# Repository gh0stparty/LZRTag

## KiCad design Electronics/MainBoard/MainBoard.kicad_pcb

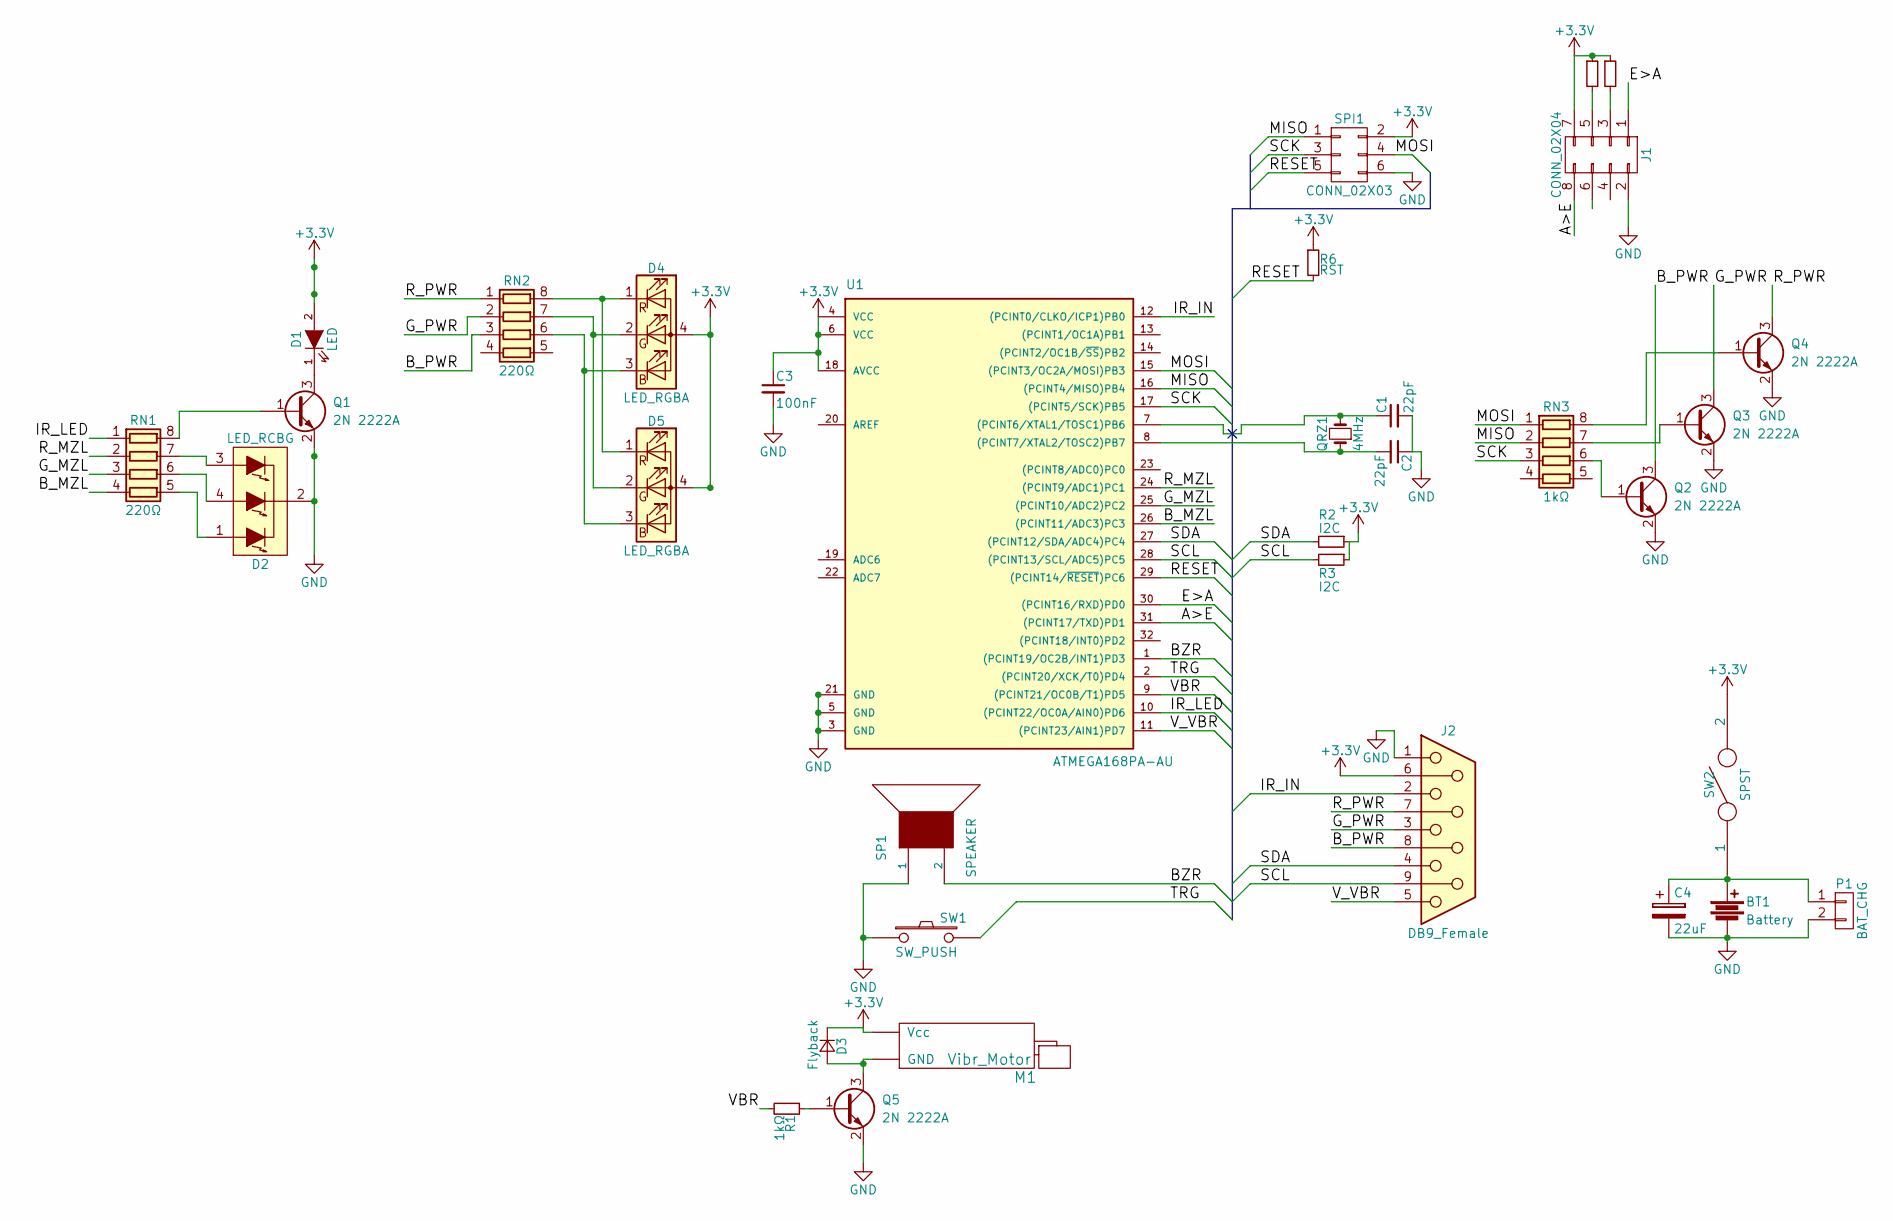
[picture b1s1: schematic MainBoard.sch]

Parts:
BT1: Battery; JST_PH_B2B-PH-K_02x2.00mm_Straight
C1, C2: 22pF; C_0603_HandSoldering
C3: 100nF; R_1210
C4: 22uF; CP_Elec_5x5.3
D1: LED; Pin_Header_Straight_1x02_Pitch2.00mm
D2: LED_RCBG; Pin_Header_Straight_1x04_Pitch2.00mm
D3: Flyback; SOD-323_HandSoldering
D4, D5: LED_RGBA; LED_Cree-PLCC4_3.2x2.8mm_CCW
J1: CONN_02X04; Pin_Header_Straight_2x04_Pitch2.54mm
J2: DB9_Female; DSUB-9_Female_Horizontal_Pitch2.77x2.84mm_EdgePinOffset4.94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
M1: Vibr_Motor; Pin_Header_Straight_1x02_Pitch2.54mm
P1: BAT_CHG; Pin_Header_Straight_1x02
Q1, Q2, Q3, Q4, Q5: 2N 2222A; SOT-23_Handsoldering
QRZ1: 4MHz; Crystal_HC49-U_Vertical
R1: 1kΩ; R_0603_HandSoldering
R2, R3: I2C; R_0603_HandSoldering
R6, R9, R11: RST; R_0603_HandSoldering
RN1, RN2: 220Ω; R_Array_Convex_4x0603
RN3: 1kΩ; R_Array_Convex_4x0603
SP1: SPEAKER; Buzzer_15x7.5RM7.6
SPI1: CONN_02X03; Pin_Header_Straight_2x03_Pitch2.54mm
SW1: SW_PUSH; Pin_Header_Straight_1x02_Pitch2.54mm
SW2: SPST; Pin_Header_Straight_1x02_Pitch2.00mm
U1: ATMEGA168PA-AU; TQFP-32_7x7mm_Pitch0.8mm

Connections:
+3V3: C3.1, D1.2 (A), D3.1 (K), D4.4 (A), D5.4 (A), J1.7, J2.6, M1.2 (Vcc), R2.1, R3.1, R6.1, R9.1, R11.1, SPI1.2, SW2.2, U1.4 (VCC), U1.6 (VCC), U1.18 (AVCC)
/A>E: J1.8, U1.31 ((PCINT17/TXD)PD1)
/BZR: SP1.2, U1.1 ((PCINT19/OC2B/INT1)PD3)
/B_MZL: RN1.4 (R4.1), U1.26 ((PCINT11/ADC3)PC3)
/B_PWR: J2.8, Q2.3 (C), RN2.3 (R3.1)
/E>A: J1.1, U1.30 ((PCINT16/RXD)PD0)
/G_MZL: RN1.3 (R3.1), U1.25 ((PCINT10/ADC2)PC2)
/G_PWR: J2.3, Q3.3 (C), RN2.2 (R2.1)
/IR_IN: J2.2, U1.12 ((PCINT0/CLKO/ICP1)PB0)
/IR_LED: RN1.1 (R1.1), U1.10 ((PCINT22/OC0A/AIN0)PD6)
/MISO: RN3.2 (R2.1), SPI1.1, U1.16 ((PCINT4/MISO)PB4)
/MOSI: RN3.1 (R1.1), SPI1.4, U1.15 ((PCINT3/OC2A/MOSI)PB3)
/RESET: R6.2, SPI1.5, U1.29 ((PCINT14/~RESET~)PC6)
/R_MZL: RN1.2 (R2.1), U1.24 ((PCINT9/ADC1)PC1)
/R_PWR: J2.7, Q4.3 (C), RN2.1 (R1.1)
/SCK: RN3.3 (R3.1), SPI1.3, U1.17 ((PCINT5/SCK)PB5)
/SCL: J2.9, R3.2, U1.28 ((PCINT13/SCL/ADC5)PC5)
/SDA: J2.4, R2.2, U1.27 ((PCINT12/SDA/ADC4)PC4)
/TRG: SW1.2, U1.2 ((PCINT20/XCK/T0)PD4)
/VBR: R1.2, U1.9 ((PCINT21/OC0B/T1)PD5)
/V_VBR: J2.5, U1.11 ((PCINT23/AIN1)PD7)
GND: BT1.2, C1.2, C2.1, C3.2, C4.2, D2.2 (COMMON_CATHODE), J1.2, J2.1, P1.2, Q1.2 (E), Q2.2 (E), Q3.2 (E), Q4.2 (E), Q5.2 (E), SP1.1, SPI1.6, SW1.1, U1.3 (GND), U1.5 (GND), U1.21 (GND)
unnamed: BT1.1, C4.1, P1.1, SW2.1
unnamed: C1.1, QRZ1.2, U1.7 ((PCINT6/XTAL1/TOSC1)PB6)
unnamed: C2.2, QRZ1.1, U1.8 ((PCINT7/XTAL2/TOSC2)PB7)
unnamed: D1.1 (K), Q1.3 (C)
unnamed: D2.1 (RED_ANODE), RN1.5 (R4.2)
unnamed: D2.3 (BLUE_ANODE), RN1.7 (R2.2)
unnamed: D2.4 (GREEN_ANODE), RN1.6 (R3.2)
unnamed: D3.2 (A), M1.1 (GND), Q5.3 (C)
unnamed: D4.1 (RK), D5.1 (RK), RN2.8 (R1.2)
unnamed: D4.2 (GK), D5.2 (GK), RN2.7 (R2.2)
unnamed: D4.3 (BK), D5.3 (BK), RN2.6 (R3.2)
unnamed: J1.3, R11.2
unnamed: J1.5, R9.2
unnamed: Q1.1 (B), RN1.8 (R1.2)
unnamed: Q2.1 (B), RN3.6 (R3.2)
unnamed: Q3.1 (B), RN3.7 (R2.2)
unnamed: Q4.1 (B), RN3.8 (R1.2)
unnamed: Q5.1 (B), R1.1

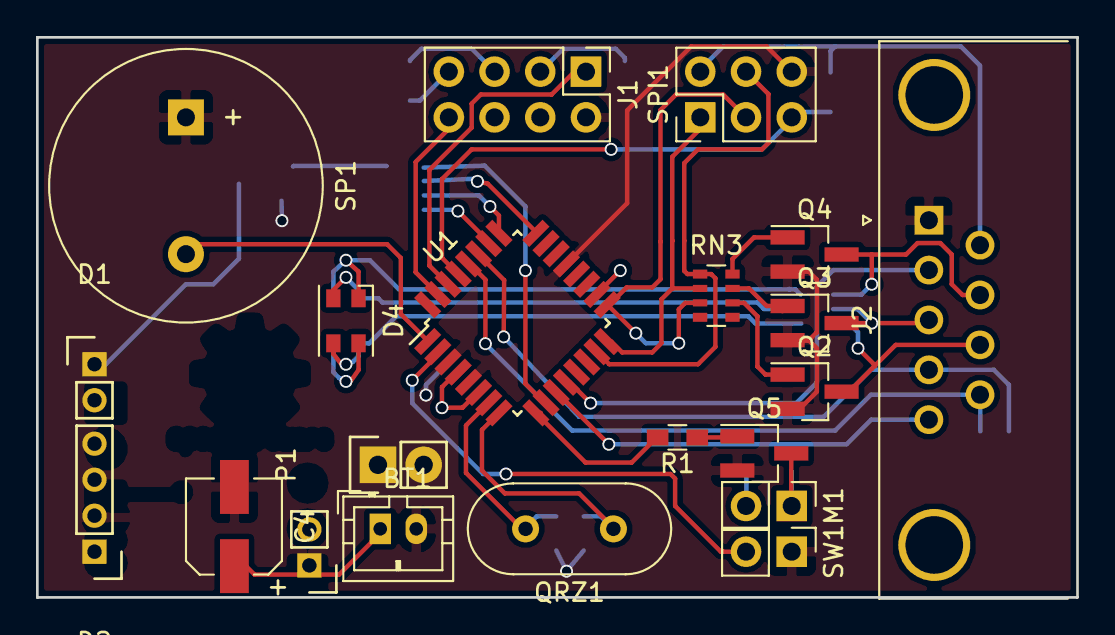
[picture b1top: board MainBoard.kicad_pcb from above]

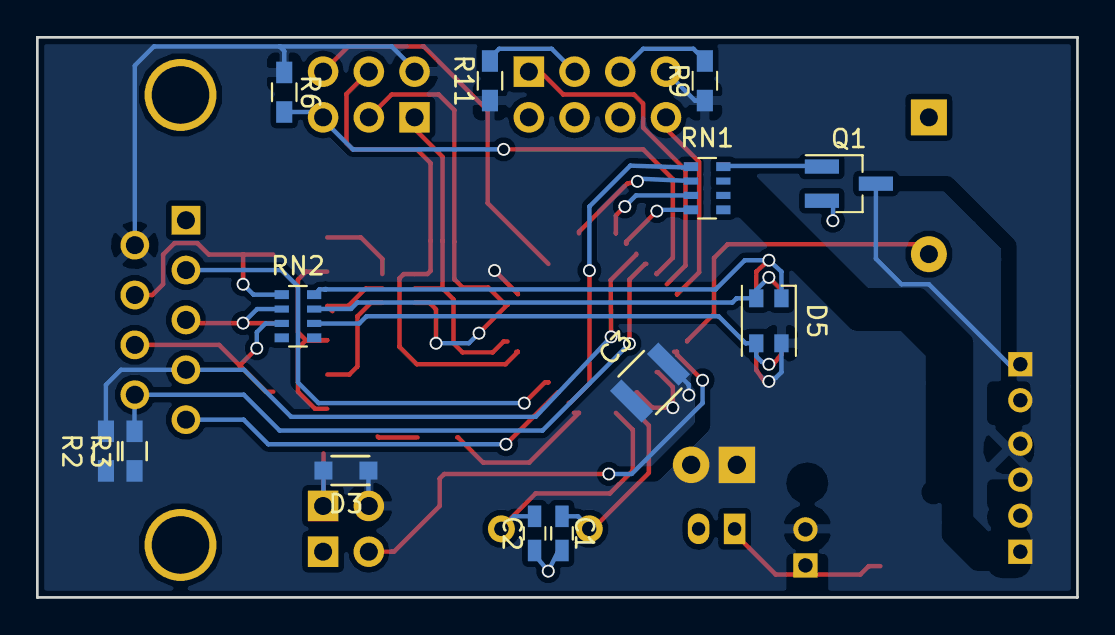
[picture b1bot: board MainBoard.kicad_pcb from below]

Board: 2 copper layers, 57.8 x 31.1 mm, 34 parts (13 on the bottom side), 40 nets.

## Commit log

2018-07-27 {Began revamp of PCB for professional manufacture!}
